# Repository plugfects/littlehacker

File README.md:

# littlehacker
Small Audio Processing board

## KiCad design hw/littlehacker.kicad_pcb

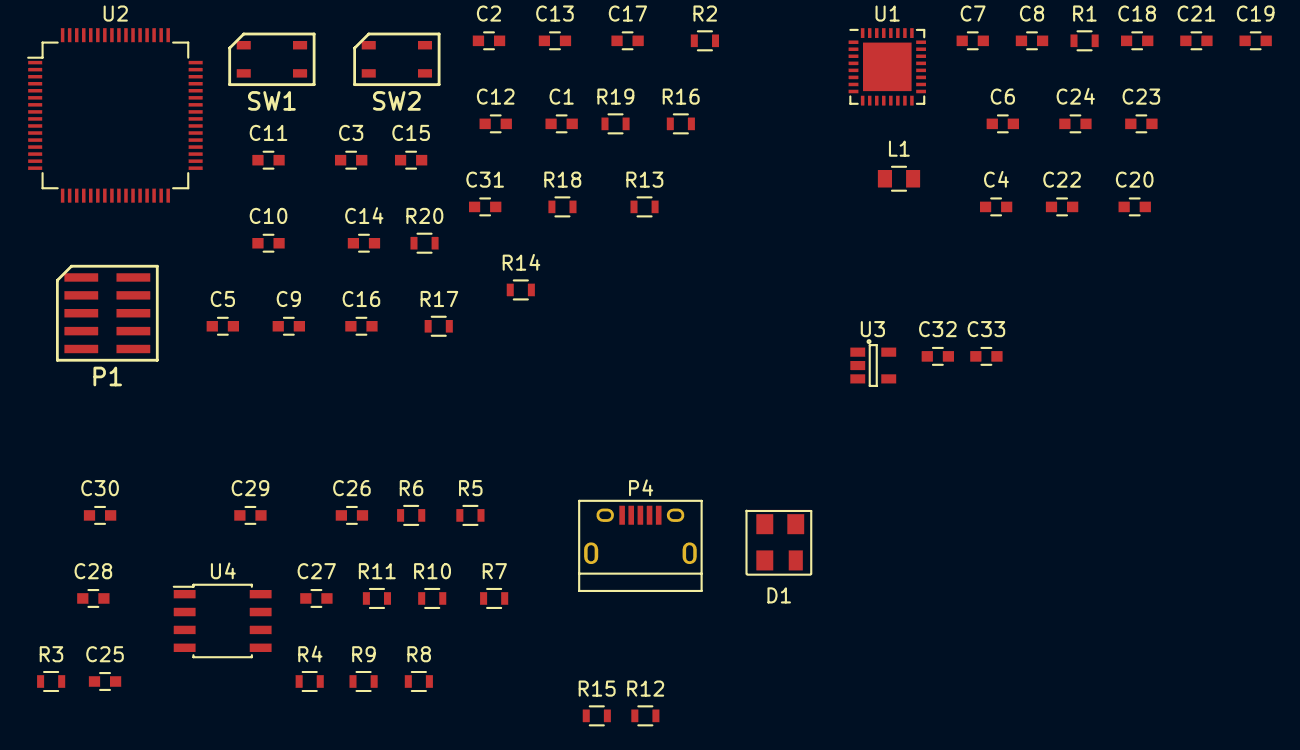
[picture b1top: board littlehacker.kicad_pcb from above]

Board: 2 copper layers, 63 parts (0 on the bottom side), 46 nets, no tracks yet.

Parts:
C1, C2: 22nF; C_0603
C3, C25, C32, C33: 1uF; C_0603
C4, C5, C18: 10uF; C_0603
C6, C9, C12, C13, C14, C15, C16, C17, C20, C22, C24, C31: 100nF; C_0603
C7, C8: 47uF; C_0603
C10, C11: 47nF-C0G; C_0603
C19, C21, C23: 22uF; C_0603
C26: 10nF; C_0603
C27: 100uF; C_0603
C28, C29: 470pF (C0G); C_0603
C30: 2700pF (C0G); C_0603
D1: PRTR5V0U2X; SOT143B
L1: 30@100MHz; C_0805
P1: CONN_01X06; CMxDBG
P4: USB_B; USB_Micro-B
R1, R12, R15, R19, R20: 10k; R_0603
R2, R13, R14, R16, R17, R18: 1K-1%; R_0603
R3, R4, R5, R6: 100k; R_0603
R7, R8, R10: 634R; R_0603
R9, R11: 91R; R_0603
SW1, SW2: SW_PUSH; tactileswitch
U1: pcm3070i; QFN-32-1EP_5x5mm_Pitch0.5mm
U2: stm32L476R; LQFP-64_10x10mm_Pitch0.5mm
U3: TLV702; SOT-23-5
U4: LME49721; SOIC-8_3.9x4.9mm_Pitch1.27mm

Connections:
/Processor/BOOT: R20.1, SW2.1, U2.60
/Processor/CAP_CH1: C10.1, U2.33
/Processor/CAP_CH4: C11.1, U2.40
/Processor/I2C3_SCL: U1.9, U2.8
/Processor/I2C3_SDA: U1.10, U2.9
/Processor/NRST: C31.1, P1.5, R19.2, SW1.2, U2.7
/Processor/SAI1_FS_A: U1.3, U2.62
/Processor/SWCLK: P1.2, U2.49
/Processor/SWDIO: P1.4, U2.46
/Sheet56FDA94B/BCLK: U1.2, U2.29
/Sheet56FDA94B/DIN: U1.4, U2.11
/Sheet56FDA94B/DOUT: U1.5, U2.57
/Sheet56FDA94B/IN2_L: U1.15, U1.21
/Sheet56FDA94B/IN2_R: U1.16, U1.20
/Sheet56FDA94B/MCLK: U1.1, U2.61
/Sheet57018DC8/AUDIO_IN_N: C30.2, R10.1, R11.2, U1.13
/Sheet57018DC8/AUDIO_IN_P: C30.1, R8.1, R9.1, U1.14
/Sheet5706764E/MISO: R12.2, U2.22
/USB/D+: D1.3, P4.2, U2.45
/USB/D-: D1.2, P4.3, U2.44
/USB/VBUS: D1.4, P4.1
GND: C1.2, C2.2, C4.2, C5.2, C6.2, C9.2, C10.2, C11.2, C12.2, C13.2, C14.2, C15.2, C16.2, C21.2, C22.2, C23.2, C24.2, C31.2, C32.2, C33.2, D1.1, L1.2, P1.3, P4.4, P4.5, R20.2, SW1.1, U1.7, U1.28, U2.18, U2.31, U2.47, U2.63, U3.2
GNDA: C3.2, C17.2, C18.2, C19.2, C20.2, C26.2, C27.2, L1.1, R3.1, R5.1, U1.17, U2.12, U4.4
unnamed: C1.1, U2.5
unnamed: C2.1, U2.6
unnamed: C7.2, U1.27
unnamed: C8.2, U1.25
unnamed: C18.1, U1.18
unnamed: C19.1, C20.1, U1.24
unnamed: C25.1, R6.2, U4.2
unnamed: C25.2, R3.2
unnamed: C26.1, C27.1, R4.1, R5.2, R6.1, U4.6
unnamed: C28.1, R7.1, R9.2, U4.1
unnamed: C28.2, R8.2, U4.3
unnamed: C29.1, R7.2, R10.2, U4.5
unnamed: C29.2, R11.1, U4.7
unnamed: R1.2, U1.30
unnamed: R2.1, U2.39
unnamed: R13.1, U2.38
unnamed: R14.1, U2.37
unnamed: R16.1, U2.36
unnamed: R17.1, U2.35
unnamed: R18.1, U2.34
VAA: C3.1, C17.1, U2.13, U4.8
VCC: C32.1, U3.1, U3.3
VDD: C4.1, C5.1, C6.1, C9.1, C12.1, C13.1, C14.1, C15.1, C16.1, C21.1, C22.1, C23.1, C24.1, C33.1, P1.1, R1.1, R4.2, R12.1, R15.1, R19.1, SW2.2, U1.6, U1.26, U1.29, U2.1, U2.19, U2.32, U2.48, U2.64, U3.5

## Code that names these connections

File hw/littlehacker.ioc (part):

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Mcu.Name=STM32L476R(C-E-G)Tx
Mcu.Package=LQFP64
Mcu.UserName=STM32L476RETx
PA11.Mode=Device_Only
PA11.Signal=USB_OTG_FS_DM
PA12.Mode=Device_Only
PA12.Signal=USB_OTG_FS_DP
PA13.Mode=Serial-Wire
PA13.Signal=SYS_JTMS-SWDIO
PA14.Mode=Serial-Wire
PA14.Signal=SYS_JTCK-SWCLK
PA5.Mode=Full_Duplex_Master
PA5.Signal=SPI1_SCK
PA6.Mode=Full_Duplex_Master
PA6.Signal=SPI1_MISO
PA7.Mode=Full_Duplex_Master
PA7.Signal=SPI1_MOSI
PA9.Mode=Activate_VBUS
PA9.Signal=USB_OTG_FS_VBUS
PB10.Mode=SAI_A_MasterWithClock
PB10.Signal=SAI1_SCK_A
PB12.Mode=G1_IO1-Sampling
PB12.Signal=TSC_G1_IO1
PB13.Mode=G1_IO2-Channel
PB13.Signal=TSC_G1_IO2
PB14.Mode=G1_IO3-Channel
PB14.Signal=TSC_G1_IO3
PB15.Mode=G1_IO4-Channel
PB15.Signal=TSC_G1_IO4
PB5.Mode=SAI_B_SyncSlave
PB5.Signal=SAI1_SD_B
PB8.Mode=SAI_A_MasterWithClock
PB8.Signal=SAI1_MCLK_A
PB9.Mode=SAI_A_MasterWithClock
PB9.Signal=SAI1_FS_A
PC0.Mode=I2C
PC0.Signal=I2C3_SCL
PC1.Mode=I2C
PC1.Signal=I2C3_SDA
PC3.Mode=SAI_A_MasterWithClock
PC3.Signal=SAI1_SD_A
PC6.Mode=G4_IO1-Channel
PC6.Signal=TSC_G4_IO1
PC7.Mode=G4_IO2-Channel
PC7.Signal=TSC_G4_IO2
PC8.Mode=G4_IO3-Channel
PC8.Signal=TSC_G4_IO3
PC9.Mode=G4_IO4-Sampling
PC9.Signal=TSC_G4_IO4
PH0/OSC_IN.Mode=HSE-External-Oscillator
PH0/OSC_IN.Signal=RCC_OSC_IN
PH1/OSC_OUT.Mode=HSE-External-Oscillator
PH1/OSC_OUT.Signal=RCC_OSC_OUT
RCC.HSE_VALUE=8000000

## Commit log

2016-03-31 Started project
2016-03-31 Acrescentada a folha do processador, add .gitignore, add littlehacker.ioc(STMCube)
2016-03-31 add waffle.io badge
2016-04-01 Added power supply sch
2016-04-03 Add analog fe, add simple linear source closes#2
2016-04-04 Changed to switched regulator
2016-04-07 USB integrated, closes #16
2016-04-08 Added USB and SD card, closes #16
2016-04-09 Footprint association, still in progress
2016-04-11 Change voltage regulator to linear
2016-04-16 Rev0 intermediary, need capacitive circuit design and stm32l476 package migration
2016-04-17 Pin assignment modified in STCube
2016-04-17 Schematics rev0 done
2016-04-26 Partial footprint and PN association
